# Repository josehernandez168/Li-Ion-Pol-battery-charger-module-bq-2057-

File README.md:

# Li-Ion-Pol-battery-charger-module-bq-2057

In this repository, design files and notes are shared on the making of a
charge management board for Lithium Ion or Polymer batteries 3.7 or 7.4 V.
This was done using the bq2057 by Texas Instruments.

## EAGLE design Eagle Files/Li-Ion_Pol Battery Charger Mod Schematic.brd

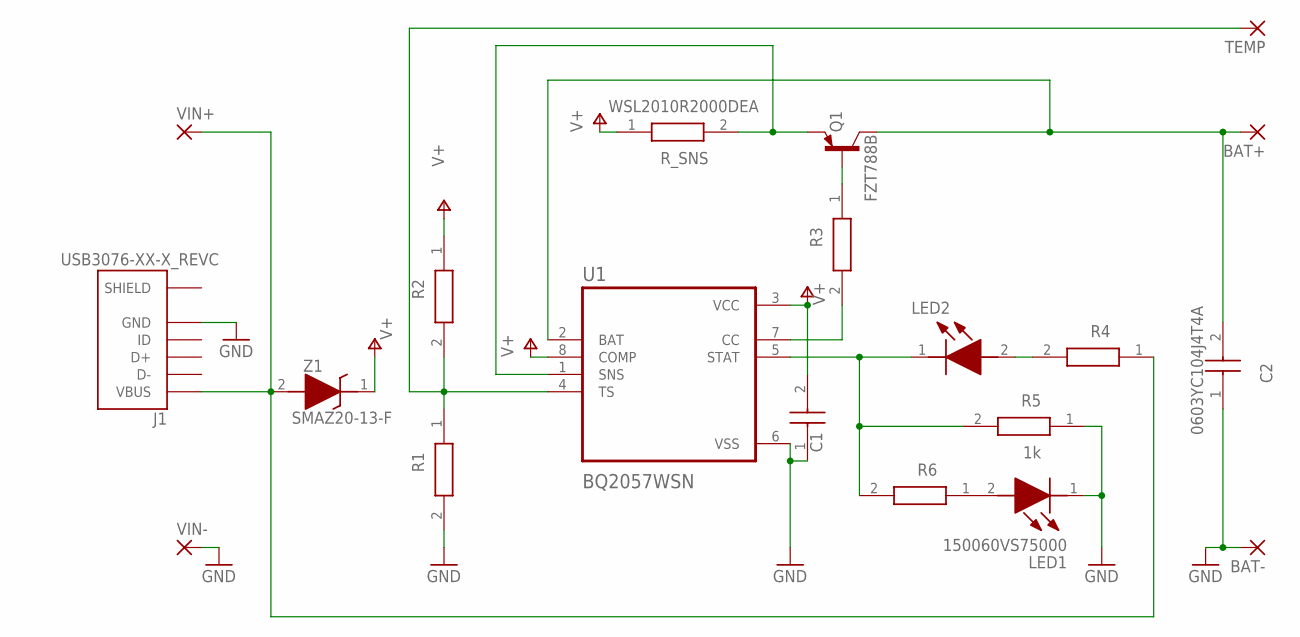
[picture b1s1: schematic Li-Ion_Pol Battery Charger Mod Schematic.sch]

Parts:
BAT+: 3,17/1,3
BAT-: 3,17/1,3
C1, C2: 0603YC104J4T4A; CAPC1608X90N
J1: USB3076-XX-X_REVC; GCT_USB3076-XX-X_REVC
LED1, LED2: 150060VS75000; LEDC1608X80N
Q1: FZT788B; SOT230P700X165-4N
R1, R5: 1k; RESC1608X55N
R2, R3, R4, R6: RS73F1JTTD1001B; RESC1608X55N
R_SNS: WSL2010R2000DEA; RESC5125X89N
TEMP: 3,17/1,3
U1: BQ2057WSN; SOIC127P599X175-8N
VIN+: 3,17/1,3
VIN-: 3,17/1,3
Z1: SMAZ20-13-F; DIOM5226X240N

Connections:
GND: BAT-.1, C1.1, C2.1, J1.5 (GND), LED1.1 (K), R1.2, R5.1, U1.6 (VSS), VIN-.1
unnamed: LED2.1 (K), R5.2, R6.2, U1.5 (STAT)
unnamed: LED2.2 (A), R4.2
unnamed: LED1.2 (A), R6.1
unnamed: Q1.1 (B), R3.1
unnamed: BAT+.1, C2.2, Q1.2 (C), Q1.4 (C), U1.2 (BAT)
unnamed: R3.2, U1.7 (CC)
unnamed: R1.1, R2.2, TEMP.1, U1.4 (TS)
unnamed: Q1.3 (E), R_SNS.2, U1.1 (SNS)
unnamed: J1.1 (VBUS), R4.1, VIN+.1, Z1.2 (A)
SHIELD: J1.6 (SHIELD), J1.7 (SHIELD), J1.8 (SHIELD), J1.9 (SHIELD), J1.10 (SHIELD), J1.11 (SHIELD)
V+: C1.2, R2.1, R_SNS.1, U1.3 (VCC), U1.8 (COMP), Z1.1 (K)

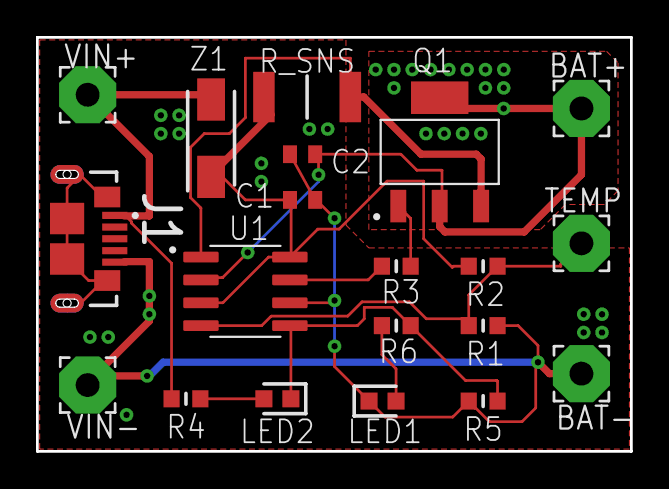
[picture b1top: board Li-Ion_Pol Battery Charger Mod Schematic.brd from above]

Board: 2 copper layers, 33.0 x 23.0 mm, 20 parts (0 on the bottom side), 12 nets.
